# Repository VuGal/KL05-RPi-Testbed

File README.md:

# FRDM-KL05Z Testbed device using Raspberry Pi 3B+
  
The project goal was to create a testbed device for FRDM-KL05Z boards. Raspberry Pi 3B+ was used to enable Python and Robot Framework usage.
The testbed board is connected to the RPi from one side and to the tested board from the other ("sandwich" connection). Also USB connection 
between RPi and KL05Z is needed to enable USB-CDC communication. Tests are launched from Linux environment on RPi. Tests included into this project
are focused on GPIO testing - all GPIO ports are tested with the exception of D0 and D1 because they are needed for correct UART communication
(it's needed anyway to test other ports so D0 and D1 behavior is fine if the UART communication works).
  
## KL05Z
Keil uVision5 was used during KL05Z code development. Output .hex file (.hex generation must be enabled in IDE settings) should be put into /home/pi/RobotWorkspace/files/ path on RPi.

Source code files description:  
<b>main.c</b> - file containing the main loop and calls of necessary initializations (GPIO, RTC, UART)  
<b>operations.c / operations.h</b></b> - handlers for commands received via UART messages  
<b>gpio.c / gpio.h</b> - GPIO initialization and functions responsible for getting and setting pin state  
<b>rtc.c / rtc.h</b> - Real-time clock (RTC) configuration  
<b>uart.c / uart.h</b> - UART initialization and functions responsible for receiving and sending message  
<b>extra.c / extra.h</b> - helper functions  

## Raspberry Pi
Requirements:  
Raspberry Pi OS - May 2021 version  
Python 3.7.3  
Python libraries: serial, RPi.GPIO  
Robot Framework 4.1  
  
Usage:  
Files should be put into /home/pi/RobotWorkspace/ path.
Starting tests: ./start.sh  
Tests are visible in robot/main.robot  
Keywords are visible in python/Keywords.py  
Results will be visible in output.xml, log.html and report.html  

## PCB

Pins of Raspberry Pi had to be connected with suitable pins of KL05Z.  
In order to implement this idea a PCB shield has been designed with usage of KiCad ver. 5.1.9.  
The 1 kΩ resistors were added in each connection to avoid current overdrive in case of different GPIO logic states on each side.

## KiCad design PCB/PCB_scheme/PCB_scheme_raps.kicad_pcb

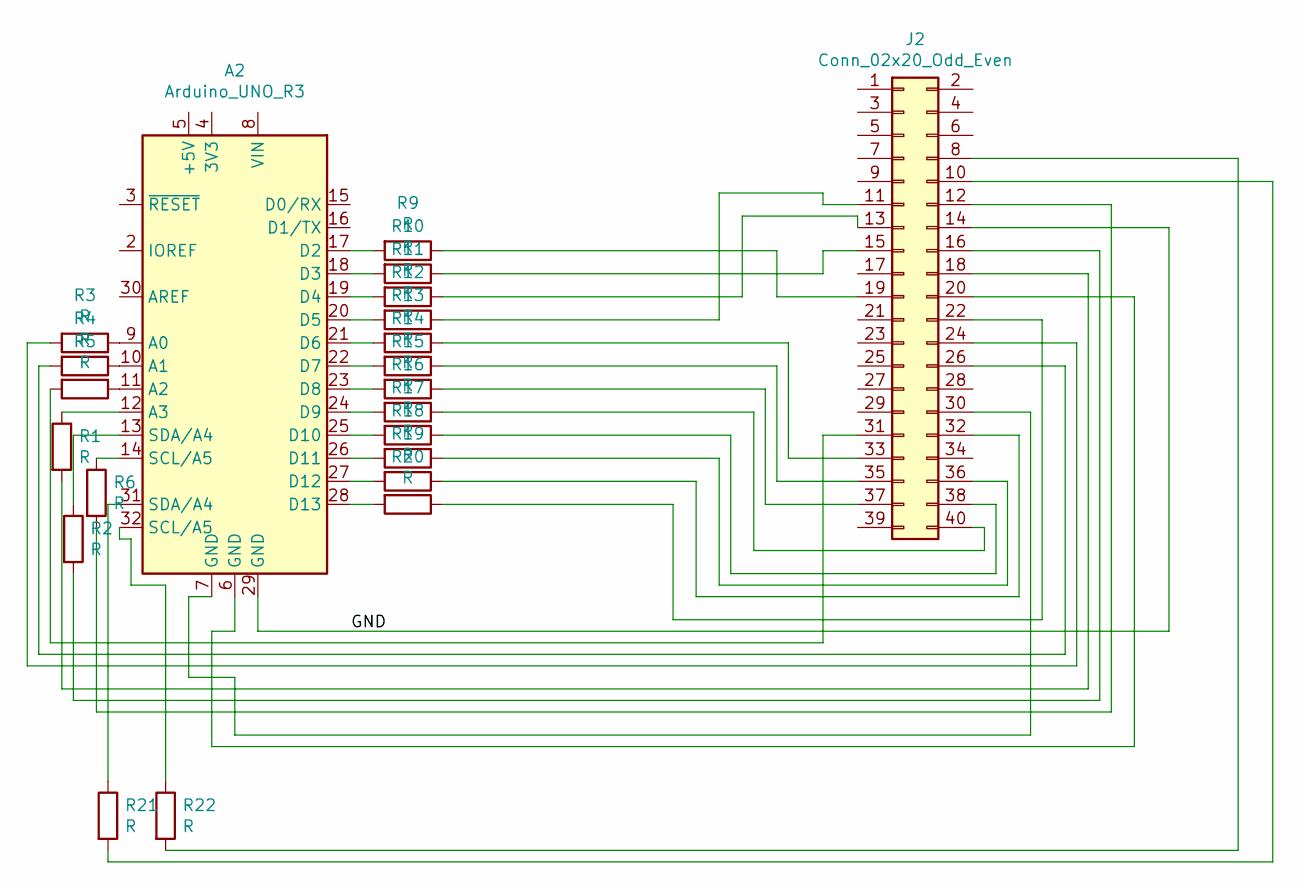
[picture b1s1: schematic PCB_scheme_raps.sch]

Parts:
A2: Arduino_UNO_R3
J2: Conn_02x20_Odd_Even; PinSocket_2x20_P2.54mm_Vertical
R1, R2, R3, R4, R5, R6, R9, R10, R11, R12, R13, R14, R15, R16, R17, R18, R19, R20, R21, R22: R; R_0603_1608Metric

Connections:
/GND: A2.29 (GND), J2.14
unnamed: A2.6 (GND), J2.20
unnamed: A2.7 (GND), J2.30
unnamed: A2.9 (A0), R3.1
unnamed: A2.10 (A1), R4.1
unnamed: A2.11 (A2), R5.1
unnamed: A2.12 (A3), R1.1
unnamed: A2.13 (SDA/A4), R2.1
unnamed: A2.14 (SCL/A5), R6.1
unnamed: A2.17 (D2), R9.2
unnamed: A2.18 (D3), R10.2
unnamed: A2.19 (D4), R11.2
unnamed: A2.20 (D5), R12.2
unnamed: A2.21 (D6), R13.2
unnamed: A2.22 (D7), R14.2
unnamed: A2.23 (D8), R15.2
unnamed: A2.24 (D9), R16.2
unnamed: A2.25 (D10), R17.2
unnamed: A2.26 (D11), R18.2
unnamed: A2.27 (D12), R19.2
unnamed: A2.28 (D13), R20.2
unnamed: A2.31 (SDA/A4), R21.1
unnamed: A2.32 (SCL/A5), R22.1
unnamed: J2.8, R22.2
unnamed: J2.10, R21.2
unnamed: J2.11, R12.1
unnamed: J2.12, R6.2
unnamed: J2.13, R11.1
unnamed: J2.15, R10.1
unnamed: J2.16, R2.2
unnamed: J2.18, R1.2
unnamed: J2.19, R9.1
unnamed: J2.22, R20.1
unnamed: J2.24, R3.2
unnamed: J2.26, R4.2
unnamed: J2.31, R5.2
unnamed: J2.32, R19.1
unnamed: J2.33, R13.1
unnamed: J2.35, R14.1
unnamed: J2.36, R18.1
unnamed: J2.37, R15.1
unnamed: J2.38, R17.1
unnamed: J2.40, R16.1

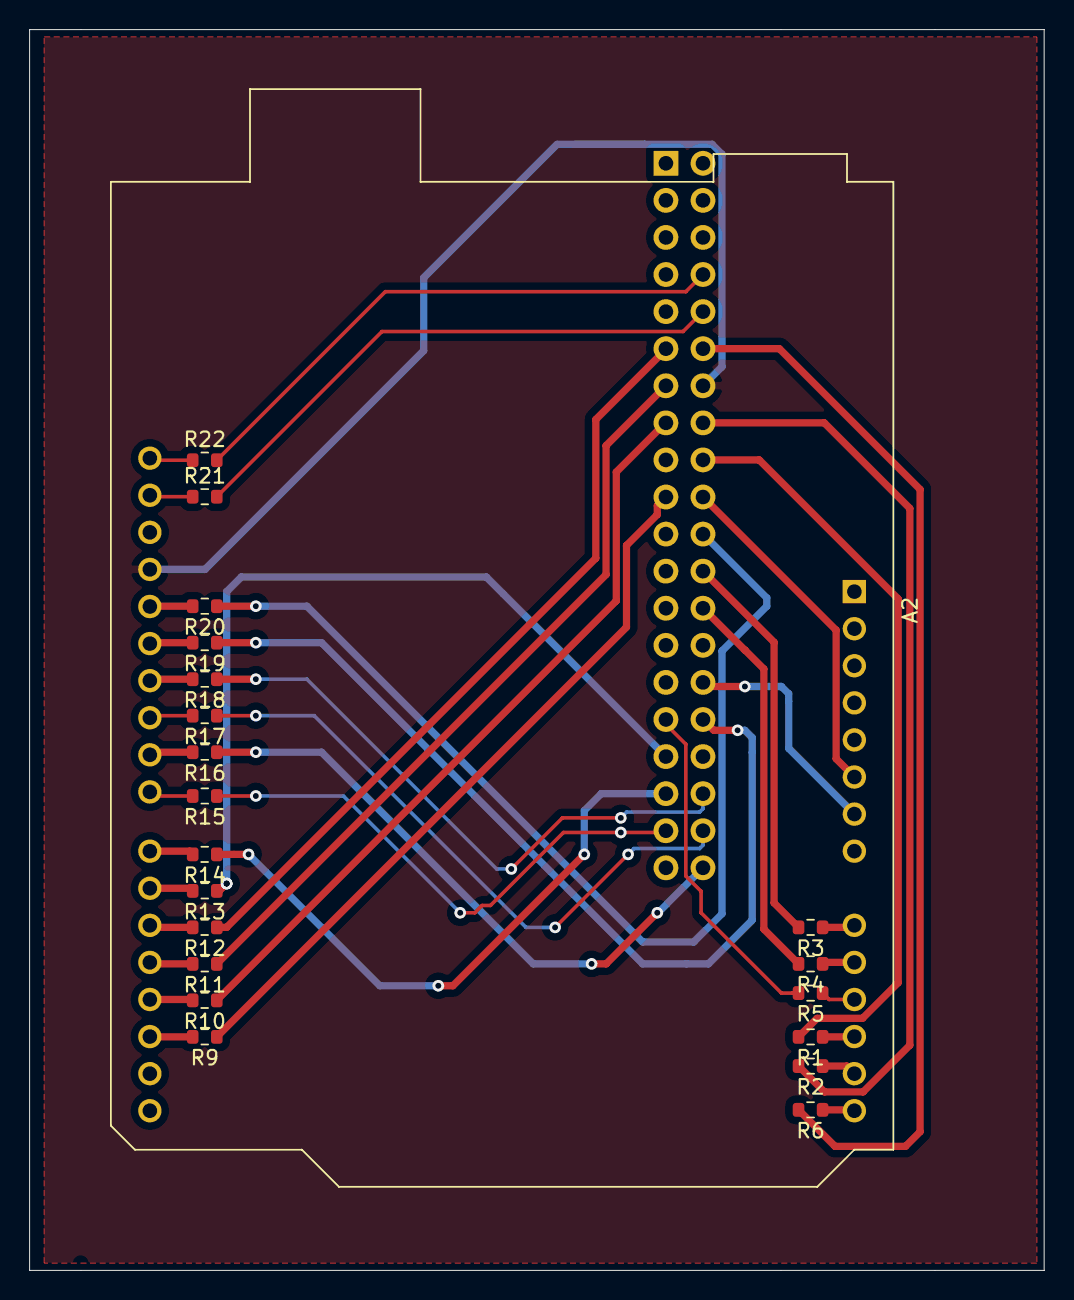
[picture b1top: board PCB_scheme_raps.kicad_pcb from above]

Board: 2 copper layers, 69.5 x 85.0 mm, 22 parts (1 on the bottom side), 43 nets.

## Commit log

2021-09-12 Create structure for future commits
2021-09-12 Add Python and Robot files
2021-09-12 Code refactor
2021-09-12 Add start.sh file
2021-09-12 Add KL05Z code
2021-09-12 Remove unused leds.c/leds.h files
2021-09-12 Correct formatting of uart.c file
2021-09-12 Add KiCad PCB scheme files
2021-09-12 KL05 code related information
2021-09-12 Change readme title
2021-09-12 Add proper newlines to readme file
2021-09-12 General description added
2021-09-12 Add PCB description
2021-09-12 Add resistor info
2021-09-12 Add info about RPi OS
2021-09-12 Add paths information
2021-09-12 Add GPIO related info
